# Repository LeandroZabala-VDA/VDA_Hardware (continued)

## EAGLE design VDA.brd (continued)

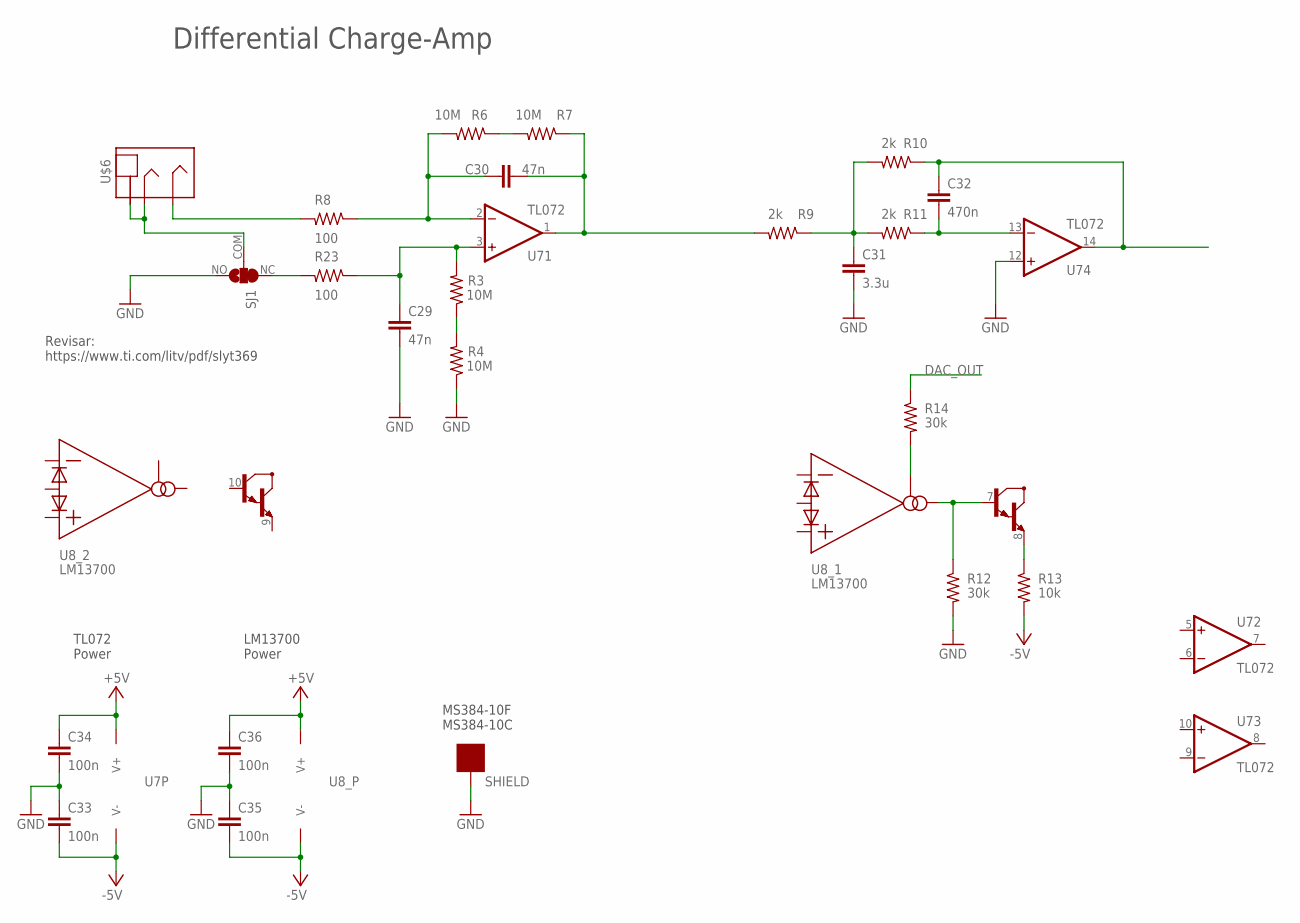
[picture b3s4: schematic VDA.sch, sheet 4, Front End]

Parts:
C29, C30: 47n; C_0603
C31: 3.3u; C_0603
C32: 470n; C_0603
C33, C34, C35, C36: 100n; C_0603
R3, R4, R6, R7: 10M; R_0603
R8, R23: 100; R_0603
R9, R10, R11: 2k; R_0603
R12, R14: 30k; R_0603
R13: 10k; R_0603
SHIELD: MS384
SJ1: SJ-PS; SJ_2
U7: TL072; SOIC127P600X175-14N
U8: LM13700; SO16
U$6: STEREO-JACK; PJ-3200

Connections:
+5V: C34.P$1 (1), C36.P$1 (1), U7.4 (V+), U8.11 (V+); also elsewhere on the board
-5V: C33.P$2 (2), C35.P$2 (2), R13.2, U7.11 (V-), U8.6 (V-); also elsewhere on the board
DAC_OUT: R14.1
GND: C29.P$2 (2), C31.P$2 (2), C33.P$1 (1), C34.P$2 (2), C35.P$1 (1), C36.P$2 (2), R4.1, R12.2, SHIELD.P$1, SHIELD.P$2, SJ1.NO, U7.12 (+IN); also elsewhere on the board
GND1: C30.P$2 (2), R7.1, R9.2, U7.1 (OUT)
unnamed: C29.P$1 (1), R3.2, R23.1, U7.3 (+IN)
unnamed: R3.1, R4.2
unnamed: C30.P$1 (1), R6.2, R8.1, U7.2 (-IN)
unnamed: R6.1, R7.2
unnamed: SJ1.COM, U$6.1 (SLEEVE), U$6.3 (RING)
unnamed: C31.P$1 (1), R9.1, R10.2, R11.2
unnamed: R12.1, U8.5 (OUT), U8.7 (B)
unnamed: C32.P$1 (1), R10.1, U7.14 (OUT)
unnamed: C32.P$2 (2), R11.1, U7.13 (-IN)
unnamed: R13.1, U8.8 (E)
unnamed: R14.2, U8.1 (AMP_BIAS)
unnamed: R8.2, U$6.2 (TIP)
unnamed: R23.2, SJ1.NC

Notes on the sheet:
TL072 Power
LM13700 Power
Revisar: https://www.ti.com/litv/pdf/slyt369
MS384-10F MS384-10C
Differential Charge-Amp

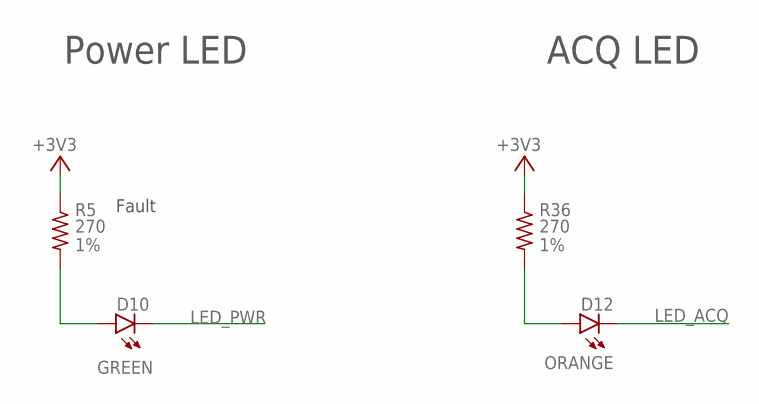
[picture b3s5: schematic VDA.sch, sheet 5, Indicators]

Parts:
D10: GREEN; LED_0603_ARROW
D12: ORANGE; LED_0603_ARROW
R5, R36: 270; R_0402

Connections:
+3V3: R5.1, R36.1; also elsewhere on the board
LED_ACQ: D12.K
LED_PWR: D10.K
unnamed: D12.A, R36.2
unnamed: D10.A, R5.2

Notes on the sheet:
Fault
Power LED
ACQ LED

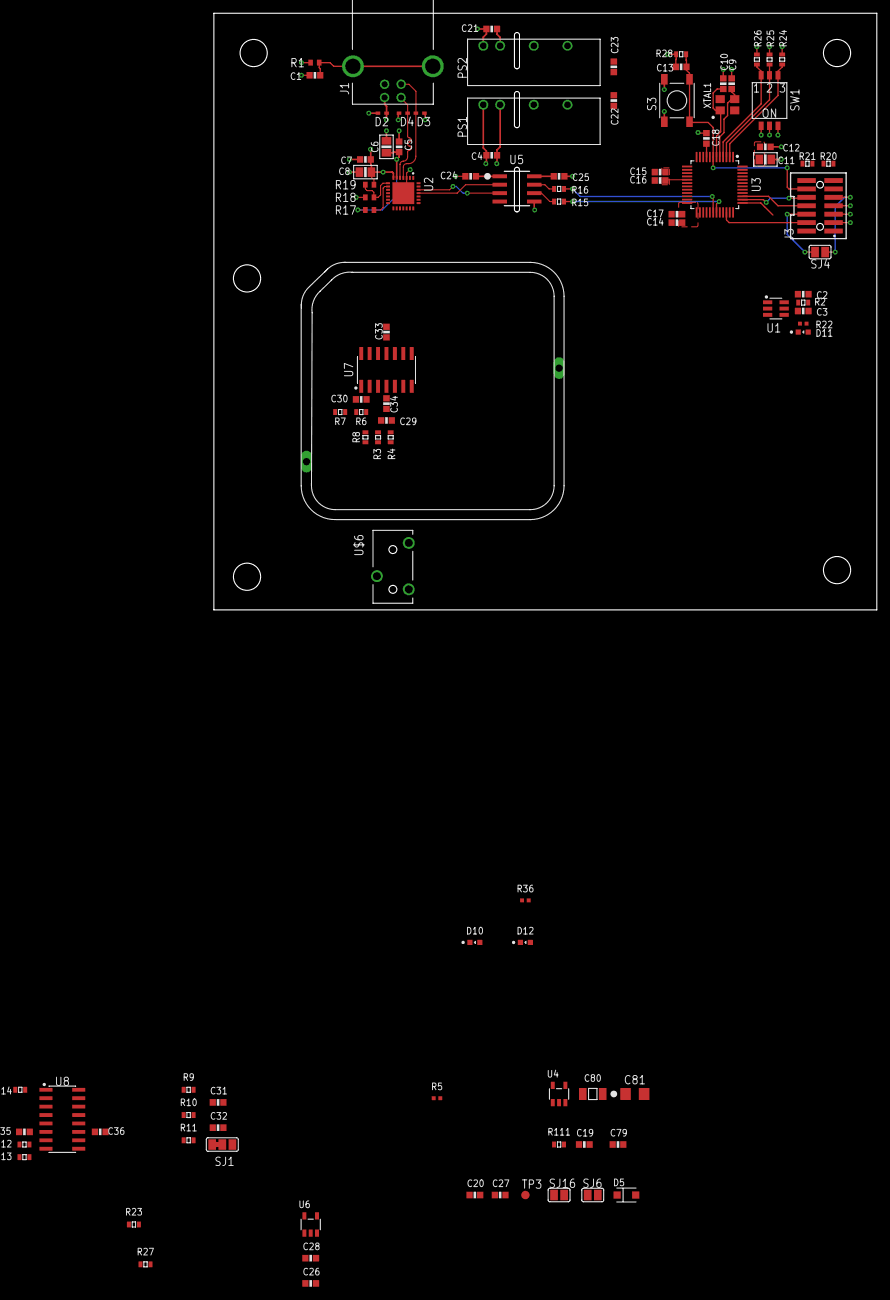
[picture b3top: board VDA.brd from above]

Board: 4 copper layers, 100.0 x 90.0 mm, 98 parts (0 on the bottom side), 57 nets.

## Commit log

2024-12-29 starting layout
2024-12-29 trabajando
2025-01-01 inicio layout
2025-01-03 trabajando en el layout
2025-01-06 panel frontal y posterior listos
2025-01-17 layout avanzado
2025-01-19 cambio de conector para expansion
2025-01-19 layout terminado
2025-01-20 trabajando en los panelizados
2025-01-20 invertí todo el panel frontal para disminuir costo de ensamblaje
2025-01-22 BOM del adquisidor listo
2025-01-22 retoques en capa tnames del adquisidor
2025-01-22 archivos listos para pcbway
2025-05-01 Archivos mas ordenados
2025-06-08 added README file
2025-06-08 readme completo
2025-06-08 readme completo cambio de fotos
2025-06-08 readme completo cambio de fotos1
2025-06-08 readme completo cambio de fotos2
2025-06-09 added license
2025-06-09 corrected readme
2025-06-09 nuevo readme
